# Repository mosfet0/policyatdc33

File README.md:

This repo is for things related to the Policy@DEF CON 33 badge. Limited edition! Only 200-ish will be made.

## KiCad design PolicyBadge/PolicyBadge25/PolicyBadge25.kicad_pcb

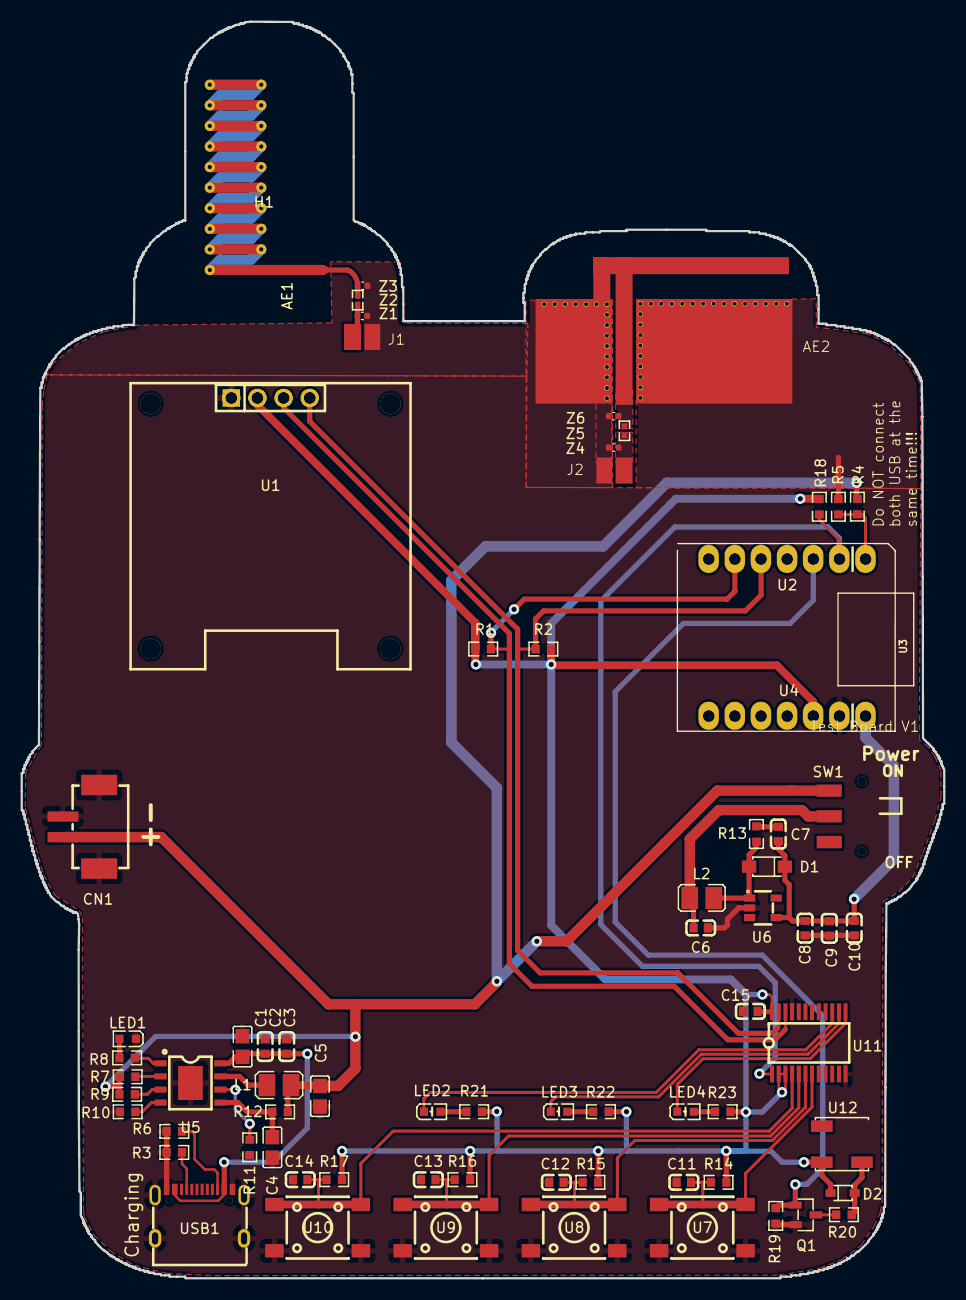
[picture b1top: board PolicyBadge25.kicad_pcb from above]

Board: 2 copper layers, 89.6 x 122.1 mm, 73 parts (0 on the bottom side), 39 nets.

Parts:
AE1: Antenna 915MHz; Texas_SWRA416_868MHz_915MHz
AE2: Antenna 2.4GHz; Cypress 2.4GHz
C1, C4, C5: 22uF; C0805
C2, C3, C8, C9, C10: 10uF; C0603
C6: 2.2uF; C0603
C7: 470pF; C0603
C11, C12, C13, C14: 0.1uF; C0603
C15: 1uF; C0603
CN1: PH2.0-2P-LT; CONN-SMD_PH2.0-1X2PW
D1: DSK26_C7502712; SOD-123FL_L2.7-W1.8-LS3.8-RD
D2: 1N5819WS; SOD-323_L1.8-W1.3-LS2.5-RD
H1: MH254V-11-04-1000; HDR-TH_4P-P2.54-V-M-3
J1: Feed Point 915MHz; Solder_Wire_Feedpoint_W65mills_S13mills
J2: Feed Point 2.4 GHz; Solder_Wire_Feedpoint_W65mills_S13mills
L1: 1uH; L2520
L2: 2.2uH; L1008
LED1: LED0603-RD_GREEN
LED2, LED3, LED4: White; LED0603-R-RD_WHITE
Q1: 2N7002; SOT-23-3_L2.9-W1.3-P1.90-LS2.4-BR
R1, R2: 4.7KΩ; R0603
R3, R6: 5.1kΩ; R0603
R4, R5: 220kΩ; R0603
R7, R8, R9: 1KΩ; R0603
R10: 51kΩ; R0603
R11: 680kΩ; R0603
R12: 0.5Ω; R0603
R13: 5.1Ω; R0603
R14, R15, R16, R17: 50kΩ; R0603
R18: 10KΩ; R0603
R19: 100KΩ; R0603
R20: 33Ω; R0603
R21, R22, R23: 2KΩ; R0603
SW1: TA-3525-A1; SW-SMD_3P-L9.1-W3.5-P2.50_BDKG-3P-H2MM
U1: HS96L03W2C03; OLED-TH_L27.8-W27.2-P2.54_C9900033791
U2, U4: HDR-TH_7P-P2.54-V-F
U3: MOUDLE-SEEEDUINO-XIAO-ESP32S3; MOUDLE14P-SMD-2.54-21X17.8MM-header-fixed
U5: IP2312-4V35; ESOP-8_L4.9-W3.9-P1.27-LS6.0-BL-EP
U6: TPS613222ADBVR; TSOT-23-5_L2.9-W1.6-P0.95-LS2.8-BR
U7, U8, U9, U10: SW-SMD_4P-L6.0-W6.0-P4.50-LS9.2
U11: TCA9555PWR; TSSOP-24_L7.8-W4.4-P0.65-LS6.4-BL
U12: YX-SMD5020; BUZ-SMD_3P_L5.0-W5.0-P3.50-TL
USB1: TYPE-C 16PIN 2MD(073); USB-C-SMD_TYPE-C-6PIN-2MD-073
Z1, Z3, Z4, Z6: R; C_0402_1005Metric
Z2, Z5: 0Ω; R0402

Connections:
/Antennas/Feed_Point_2.4GHz: J2.1 (In), Z4.1, Z5.1
/Antennas/Feed_Point_915MHz: J1.1 (In), Z1.1, Z2.1
/Batt/VIN: C1.2, C2.2, C3.2, U5.8 (VIN), USB1.2 (VBUS), USB1.11 (VBUS)
/Boost Reg/5V_OUT: C7.2, C8.2, C9.2, C10.2, D1.1 (K), U3.14 (5V), U4.1, U6.4 (VOUT)
/IO Expander and LED's/BUZZER: Q1.1 (G), R19.2, U2.3, U3.3 (PA10_A2_D2)
/IO Expander and LED's/IO_INT: R18.1, U2.2, U3.2 (PA4_A1_D1), U11.1 (~INT)
/SCL: H1.3, R1.1, U1.3 (SCL), U2.6, U3.6 (PA9_A5_D5_SCL), U11.22 (SCL)
/SDA: H1.4, R2.1, U1.4 (SDA), U2.5, U3.5 (PA8_A4_D4_SDA), U11.23 (SDA)
/VBATT+_SWITCHED: C6.2, L2.1, SW1.2 (B)
GND: AE2.2 (GND_Plane), C1.1, C2.1, C3.1, C4.1, C5.1, C6.1, C8.1, C9.1, C10.1, C11.1, C12.1, C13.1, C14.1, C15.1, CN1.1, CN1.3, CN1.4, H1.1, J1.2 (Ext), J2.2 (Ext), LED1.1 (K), Q1.2 (S), R3.1, R5.1, R6.1, R10.1, R11.1, R19.1, U1.1 (GND), U3.13 (GND), U4.2, U5.9 (EP), U6.2 (GND), U7.1, U7.2, U8.1, U8.2, U9.1, U9.2, U10.1, U10.2, U11.12 (GND), U11.21 (A0), USB1.1 (GND), USB1.12 (GND), USB1.13 (SHELL), USB1.14 (SHELL), Z1.2, Z3.2, Z4.2, Z6.2
unnamed: AE1.1 (A), Z2.2, Z3.1
unnamed: AE2.1 (A), Z5.2, Z6.1
unnamed: C7.1, R13.2
unnamed: D1.2 (A), L2.2, R13.1, U6.1 (SW)
unnamed: D2.2 (A), R20.2, U12.2 (-)
unnamed: LED1.2 (A), R8.2
unnamed: LED2.1 (A), R21.1
unnamed: LED2.2 (K), U11.15 (P12)
unnamed: LED3.1 (A), R22.1
unnamed: LED3.2 (K), U11.14 (P11)
unnamed: LED4.1 (A), R23.1
unnamed: LED4.2 (K), U11.13 (P10)
unnamed: Q1.3 (D), R20.1
unnamed: R4.1, R5.2, U2.1, U3.1 (PA02_A0_D0)
unnamed: C4.2, R12.1, U5.5 (BAT)
unnamed: R8.1, U5.1 (D1)
unnamed: R9.2, U5.3 (D2)
unnamed: R11.2, U5.6 (ICHG)
unnamed: R10.2, U5.4 (NTC)
unnamed: L1.1, U5.7 (SW)
unnamed: R7.1, U5.2 (TEST)
unnamed: C14.2, R17.2, U10.3, U10.4, U11.4 (P00)
unnamed: C13.2, R16.2, U9.3, U9.4, U11.5 (P01)
unnamed: C12.2, R15.2, U8.3, U8.4, U11.6 (P02)
unnamed: C11.2, R14.2, U7.3, U7.4, U11.7 (P03)
unnamed: R3.2, USB1.4 (CC1)
unnamed: R6.2, USB1.10 (CC2)
VBATT+: C5.2, CN1.2, L1.2, R4.2, R7.2, R9.1, R12.2, SW1.3 (C)
VCC_3V3: C15.2, D2.1 (K), H1.2, R1.2, R2.2, R14.1, R15.1, R16.1, R17.1, R18.2, R21.2, R22.2, R23.2, U1.2 (VCC), U3.12 (3V3), U4.3, U11.2 (A1), U11.3 (A2), U11.24 (VCC), U12.1 (+)

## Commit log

2025-05-31 Add policy badge schematic
2025-05-31 IO sheet
2025-06-01 update with jlcpcb parts
2025-06-09 Use IP2312 battery management ic
2025-06-20 Released version of PCB
2025-06-27 Fixes Needed
    Dim LED
    Fix the routing of 3.3V shorting two pins
    Add resistor divider to A0 for battery management.
2025-06-27 Added batt monitoring
2025-06-27 Updated PCB routing
2025-07-06 modified libraries to mosfet local
2025-07-06 minor updates
    imported new switch footprint and schematic symbol. sync'ed the PCB to add R23, R5, R6. annotated.
2025-07-06 battery silk screen + Lanyard
    added battery silk screen outline (23mmx34mm is battery, silk screen rectangle is 25x36mm). also added edge cuts for the lanyard holes.
2025-07-06 removed U5 switch
2025-07-06 removed U5 switch from schematic
2025-07-07 Lots of changes, laying out board for board shape
    Updated switches
    Added headers for XAIO
    Fixed Batt Connector polarity
    10K pullup on int
    Batt monitor resistor divider
    Fix buzzer trace
2025-07-07 Adjusted a designation to verify latest was pushed to branch
